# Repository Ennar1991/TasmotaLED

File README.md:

# TasmotaLED
Simple 12 V LED driver using an ESP-01S or compatible board for driving simple 12 V LED strips

Use any standard Tasmota build. I recommend using Fade and Speed commands to make the lights more pleasant.

Tasmota Template:
{"NAME":"TasmotaLED","GPIO":[32,0,416,0,0,0,0,0,0,0,0,0,0,0],"FLAG":0,"BASE":18}

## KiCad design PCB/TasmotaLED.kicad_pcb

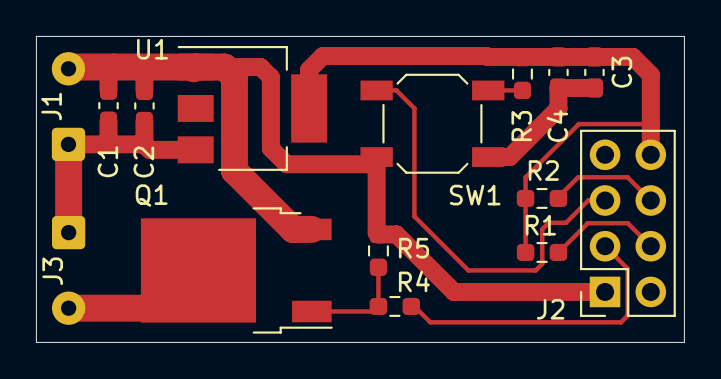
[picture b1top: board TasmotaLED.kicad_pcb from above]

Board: 2 copper layers, 36.0 x 17.0 mm, 15 parts (0 on the bottom side), 9 nets.

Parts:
C1, C3: 100n; C_0603_1608Metric_Pad1.08x0.95mm_HandSolder
C2: 1u; C_0603_1608Metric_Pad1.08x0.95mm_HandSolder
C4: 22u; C_0603_1608Metric_Pad1.08x0.95mm_HandSolder
J1: PWR_IN; SolderWire-0.25sqmm_1x02_P4.2mm_D0.65mm_OD1.7mm
J2: ESP-01S; PinSocket_2x04_P2.54mm_Vertical
J3: LED_OUT; SolderWire-0.25sqmm_1x02_P4.2mm_D0.65mm_OD1.7mm
Q1: KIA30N06B; TO-252-2
R1, R2, R3, R5: 10k; R_0603_1608Metric_Pad0.98x0.95mm_HandSolder
R4: 470; R_0603_1608Metric_Pad0.98x0.95mm_HandSolder
SW1: SW_Push; SW_SPST_SKQG_WithStem
U1: AMS1117-3.3; SOT-223-3_TabPin2

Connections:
+3V3: C3.1, C4.1, J2.8, R1.2, R2.2, R3.2, U1.2
+12V: C1.1, C2.1, J1.1, J3.1, U1.3
/LED_ON: J2.3, R4.2
/~BTN: J2.5, R3.1, SW1.2
GND: C1.2, C2.2, C3.2, C4.2, J1.2, J2.1, Q1.3, R5.2, SW1.1, U1.1
unnamed: J2.4, R1.1
unnamed: J2.6, R2.1
unnamed: J3.2, Q1.2
unnamed: Q1.1, R4.1, R5.1

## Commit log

2022-10-25 PCB Layout based on handmade prototype
2022-10-25 Template added
2022-10-25 Flipped ESP01S module 180 degrees to make module smaller and wiring simpler. Button is now below module and might need to be replaced with a side-actuated one.
